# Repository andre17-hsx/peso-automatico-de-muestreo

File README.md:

# Automatic sampling scale reader

Automatically read the value shown by a **price-computing scale** (`ACS-JC36CV28` main board +
`WP-91110-2540-V7` display board, `CS2540` chip) and send it to a sampling system.

## Web panel

The ESP creates its own WiFi network and serves a mobile-first panel, with no internet or apps
needed: a replica of the scale's LED display, history grouped by BIN and mesh, CSV export,
light/dark mode and status alerts. The panel's user interface is in Spanish.

<table>
  <tr>
    <td align="center"><br><sub>Light mode</sub></td>
    <td align="center"><br><sub>Dark mode</sub></td>
    <td align="center"><br><sub>History by BIN and mesh</sub></td>
  </tr>
  <tr>
    <td align="center"><br><sub>Alert when a mesh is completed</sub></td>
    <td align="center"><br><sub>"SIN SEÑAL" (no signal) alert</sub></td>
    <td></td>
  </tr>
</table>

<sub>Screenshots with sample data: the real panel fed by a simulated ESP, not real measurements.</sub>

## Chosen approach: tap the display bus

Over **2 wires** (`DA` = data, `SL` = clock), the main board sends the display board the content
of the 3 displays (WEIGHT 5 digits, PRICE 5, TOTAL 6 = **16 digits**).
The `CS2540` chip is equivalent to a **TM1640**.

Listening to those 2 lines **passively** gives the exact value the scale shows, without touching
the measuring circuit and without the lighting/OCR problems of a camera.

No logic analyzer is needed: an **ESP32 / ESP32-S3** acts as the sniffer.

## Sketches

| Folder | Board | What it does |
|---|---|---|
| [`sniffer_tm1640/`](sniffer_tm1640/) | any ESP32/ESP32-S3 (Heltec V3) | sniffer only; dumps the display RAM over USB serial. Used to reverse-engineer the protocol. |
| [`peso_balanza_cam/`](peso_balanza_cam/) | **ESP32-S3 Super Mini** | **Final firmware**: bus sniffer + weighing history with meshes/BIN + web panel over WiFi. |

> Sniffer on **GPIO1 (SL) / GPIO4 (DA)**, with a **Schottky diode** in series on DA in addition
> to the 470 Ω resistor. Arduino IDE: "ESP32S3 Dev Module", 4 MB flash, PSRAM `Disabled`,
> **USB CDC On Boot `Enabled`** (the board has no CH340).
> See [`peso_balanza_cam/README.md`](peso_balanza_cam/README.md) (in Spanish).

## Phase 1 — Reverse-engineering the protocol (`sniffer_tm1640/` sketch)

### How it is tapped and decoded

The scale's numbers are **7-segment LEDs**. The main board does not send the display the number
"41.30", but **which segments to light in each digit**, over a 2-wire bus understood by the
`CS2540` chip (TM1640 family):

- `SL` = clock: each bit is valid on the **rising edge** of `SL`. `DA` = data: 8 bits per byte,
  **least significant bit first**.
- **START** = `DA` falls while `SL` is high · **STOP** = `DA` rises while `SL` is high (like I²C,
  but without ACK).
- The frame that matters starts with `0xC0 | address` and continues with **1 byte per digit** (16 in
  total: the display "RAM"). Mode (`0x40`) and brightness (`0x80…0x8F`) commands are ignored.

One display update at a glance (the ESP only listens, it never sends anything):

<p align="center">
  <picture>
    <source media="(prefers-color-scheme: dark)" srcset="docs/trama-oscuro.svg">
    
  </picture>
</p>

**Tapping = listening without touching.** `SL` and `DA` go into two ESP32 pins (with 470 Ω in
series, a Schottky diode on `DA` and a common GND) and the ESP **never writes to the bus**. Two
interrupts do all the work:

1. **Rising edge of `SL`** → read `DA` and build the byte bit by bit.
2. **`DA` change while `SL` is high** → START (a frame begins) or STOP (it ends, and its bytes are
   copied to a 16-byte mirror RAM).

The bus clock is about 140 kHz, so a normal ESP32-S3 interrupt keeps up without special hardware.
The copy is read once the bus has been quiet for a few milliseconds, so a half-finished refresh
is never read.

**Decoding = turning those 16 bytes into numbers:**

| Bytes | Field | Digits |
|---|---|---|
| 0–4 | WEIGHT | 5 |
| 5–9 | UNIT PRICE | 5 |
| 10–15 | TOTAL PRICE | 6 (on the board the last two are swapped: 15 comes before 14) |

- **Byte → digit:** bits 0–6 are segments `a`–`g` and bit 7 is the decimal point. A 7-segment
  table translates it (`0x3F` = "0", `0x06` = "1", `0x7F` = "8"…), including "blank" and the
  "−" sign (segment `g` only).
- **Digits → value:** the digits are joined right-aligned within the field and the decimal point
  is placed (WEIGHT and TOTAL: 2 fixed decimals; PRICE: wherever the scale lights the point, or an
  integer).
- **Robustness:** an icon (NET/TARE…) overlapping a digit is tolerated (1 segment of difference),
  and for what the panel shows, a refresh corrupted by noise is discarded because it differs from
  its neighbours. "Stable" is not on the bus: the ESP computes it when the weight has been the
  same for 4 refreshes in a row.

Which byte is which digit and which bit is which segment is exactly what the procedure below
finds out; on this scale it turned out to be the standard mapping (`a` = bit 0 … `g` = bit 6,
point = bit 7).

### Wiring (3 wires)

| Scale (DIS connector) | → | ESP32 |
|---|---|---|
| `DA`  | `[470 Ω]` | GPIO `PIN_DA` (default 4) |
| `SL`  | `[470 Ω]` | GPIO `PIN_SL` (default 5) |
| `GND` | — | `GND` (common ground, **required**) |

- Do **NOT** connect `VCC_DIS`.
- 3 V logic → goes straight into the ESP32-S3 GPIO, no level shifter needed.
- Recommended: a **Schottky diode** (BAT54 / 1N5817) in series on `DA`, anode toward the scale
  (see `peso_balanza_cam/README.md`, section 2).
- During the test: scale on **its own battery** (not the mains charger), ESP32 over USB.
- Set `PIN_DA` / `PIN_SL` in the `.ino` to two free GPIOs of your board (range 0–31).

### Procedure

1. Flash `sniffer_tm1640.ino`. Open the Serial Monitor at **115200**.
2. **Turn on the scale** → the segment self-test is captured (all segments on).
3. Enter **known** values and write down what each display shows at each moment:
   - empty and at zero
   - reference weight (e.g. 500 g) → `0.500`
   - another weight → `1.234`
   - price on the keypad: `1.00`, `9.99`, `12.50`
   - unstable vs stable platform (STABLE icon)
   - tare / zero
4. Copy the **whole** log and analyze it to deduce:
   - which byte (`D00`–`D15`) corresponds to which physical digit of which display
   - which bit of each byte is which segment (a–g) and which is the decimal point
   - which leftover bits are icons (`kg`/`lb`, STABLE, ZERO, TARE, NET, battery…)

Serial Monitor commands: `d` normal · `c` raw transactions · `f` statistics ·
`r` raw edge dump (only if decoding comes out as garbage).

## Phase 2 — Final firmware (done: `peso_balanza_cam/`)

With the map from Phase 1, the firmware:
- Listens passively → rebuilds the 16 bytes on every refresh.
- Applies the map → WEIGHT, PRICE, TOTAL, decimal points, and works out whether the weight is
  stable.
- Detects when a tray is removed and saves **one weighing** (it tells a tare from a real
  removal); all weighings are kept (they survive power cuts) until *Borrar todo* (clear all) is
  pressed: the last 120 in NVS and the full history in a file in flash (LittleFS).
- Captures the value with a **tolerant window** (it accepts the weight even if the product drips
  or the load cell bounces, and never saves a value from the drop to zero when the tray is
  removed).
- Keeps a **diagnostic log** in RAM (`/log`, downloadable from the phone): weighings saved/lost
  and why, WiFi connections and signal, reboots, program stalls.
- The panel shows a red **"SIN SEÑAL"** (no signal) bar when it stops receiving data from the
  ESP.
- Groups the weighings into **meshes and BINs** with targets typed in by the operator, and shows
  a pop-up when a group is closed.
- Publishes everything over WiFi on a **web panel** (the board creates its own network) and
  exports CSV.

Pending: sending to an external server (MQTT / HTTP). There is a ready hook, `weighOnCommit()`,
that fires once for every confirmed weighing.

### Assembly

The scale's metal housing blocks WiFi: the ESP32-S3 goes in an **external plastic box**, powered
from the scale's battery through a buck-boost converter (TPS63020) at 3.3 V. Two 5 V fans, each
switched by a 2N2222, cool the box according to the chip temperature. Full wiring diagram of the
box:

<p align="center">
  <picture>
    <source media="(prefers-color-scheme: dark)" srcset="docs/esquema-caja-oscuro.svg">
    
  </picture>
</p>

Details (materials, polarities, transistor calculation) are in the *Alimentación y montaje* and
*Ventilación de la caja* sections of `peso_balanza_cam/README.md` (in Spanish).

### Printed circuit board

The box circuit is also designed as a 2-layer through-hole PCB (KiCad 10, generated by script,
with ERC, DRC and schematic-to-PCB parity at zero). There are three versions in
[`hardware/pcb/`](hardware/pcb/):

| Version | Size | What changes |
|---|---|---|
| [v1](hardware/pcb/) | 70 × 50 mm | TPS63020 module off-board, connected through a 4-way terminal block |
| [v2](hardware/pcb/v2/) | 96 × 53 mm | All terminal blocks in one row on one edge; TPS63020 module mounted on the board |
| [v3](hardware/pcb/v3/) | 70 × 50 mm | v1 with the TPS63020 module mounted on the board |

## If the interrupt-based sniffer loses bits

Symptoms: the 16 bytes are inconsistent between refreshes, or the self-test does not give
`0xFF` in all of them.

Options, in order:
1. Use the `r` command and send the raw edge dump → it is decoded offline.
2. Version with hardware capture (the ESP32-S3 **I2S / LCD_CAM** peripheral, `SL` as clock,
   `DA` as data, via DMA) — immune to the bus speed.
3. Raspberry Pi Pico (~€4) as a logic analyzer with sigrok firmware (*pico logic analyzer*
   project), easier to get than a Saleae.

## Last resort: camera + OCR

Reading the display with a camera (classic 7-segment recognition) was tried before moving to the
sniffer, and was dropped: the sniffer gives the **exact** value straight from the bus, without
depending on light or framing, so it is the only method left in `peso_balanza_cam/`. If the camera
approach were ever needed again, it is in the git history (commits before the 2026-10-01
cleanup). If the bus cannot be tapped on a different scale, the idea would still be valid: an
ESP32-CAM fixed in front of the display, locked exposure, a ROI crop per digit, validation over
several frames (and, if the digits confuse 3/5/6/8/9, a trained CNN instead of segment decoding).

## License

Code published **for reference and as a work sample (portfolio) only**. All rights reserved: it
may not be copied, modified, redistributed, sold or used in other projects without written
permission. Details in [`LICENSE`](LICENSE).

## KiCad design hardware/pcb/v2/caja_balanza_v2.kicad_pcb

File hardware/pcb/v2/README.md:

# Box PCB (v2): terminal blocks in one row, TPS63020 on the board

Same circuit as v1 (parent folder) with three changes:

1. **All terminal blocks in one row** on the bottom edge, with the wire entry facing outward.
2. **The TPS63020 module is mounted on the board** (U2), like the ESP, instead of terminal block J3.
3. R2 and R4 (10k) lie flat, like the other resistors.

2-layer board, **96 × 53 mm** (v1 is 70 × 50 mm).

```
 ┌──────────────────────────────────────────────────────────────────────────────┐
 │  FAN1     FAN2   │  ESP32-S3 (USB-C up)      │ C2  ┌─ U2 TPS63020 ──────┐  C8 │
 │  R 470    R 470  │                           │ C3  │ OUTPUT     INPUT   │     │
 │  R 10k    R 10k  │                           │     └────────────────────┘     │
 │  Q1       Q2     │                           │                C1   F2         │
 │  C5       C6     │   sniffer: R5 R6 D3       │   F1                           │
 │  D1       D2     │                           │                   C4   C7      │
 │ [FAN1] [FAN2]    │      [DISPLAY]            │ [BAT] [SW]                     │
 └──────────────────────────────────────────────────────────────────────────────┘
```

| Terminal block | Terminals (left → right) | Goes to |
|---|---|---|
| J4 | FAN1+, FAN1- | Fan 1 |
| J5 | FAN2+, FAN2- | Fan 2 |
| J6 DISPLAY | SL, DA, GND | Display connector |
| J1 BATERIA | BAT+, BAT- | Scale battery |
| J2 INTERRUPTOR | SW, SW | Panel switch |

Each terminal has its name printed on both sides of the board: above the screw and below the pad.
The silkscreen is in Spanish (BATERIA = battery, INTERRUPTOR = switch, VENTILADORES = fans,
ENTRADA = input, SALIDA = output).

## TPS63020 module (U2)

- It is **rotated 180°** relative to how its own silkscreen reads: the **output (OUT, GND) is on
  the left**, toward the ESP, and the **input (VIN, GND) on the right**. The board shows the
  module outline and the SALIDA / ENTRADA, VIN and OUT labels; the square pad is VIN.
- It is mounted with **4 male pins** soldered into the module's corner holes. The pins are either
  soldered straight to the board, or plugged into 4 loose female sockets if it must be removable.
- **Output jumper on 3V3** (the module's 3V3 / 4V2 / 5V pads). Check it before plugging in the
  ESP: 4V2 or 5V will damage it.
- EN and PS are not connected: the module already handles them (it starts enabled). If it gives no
  output when tested, tie EN to VIN on the module itself.
- The recommendations of TI's TPS63020 datasheet (section 10.1) are followed. The ones internal to
  the regulator (inductor, capacitors right at the chip, control ground and FB divider) are
  already met by the module. On this board:
  - C8 (10 µF) sits right at the module's VIN, and C2 (470 µF) and C3 (100 nF) at its output and
    at the ESP's 3V3 pin.
  - The 3V3 track is about 15 mm long (in v1 it was about 70 mm through the terminal block and the
    wires).
  - Wide tracks: VBAT 1.0 mm, 3V3 0.8 mm.
  - Both module grounds go straight into the ground plane, which covers both layers.
  - The display signals run far from the module.

**Measure before ordering:** the centre-to-centre distance between the module's holes. The board
uses **24.0 mm** (horizontal) × **12.4 mm** (vertical), estimated from a photo. If they do not
match, change `TPS_DX` and `TPS_DY` in `gen_pcb_v2.py` and regenerate.

## Files

| File | Purpose |
|---|---|
| `fab/caja_balanza_v2_gerber_JLCPCB.zip` | Gerbers and drill files for JLCPCB / PCBWay |
| `esquema_caja_balanza_v2.pdf` | v2 schematic |
| `caja_balanza_v2.kicad_pro` | KiCad 10 project (linked board and schematic) |
| `BOM.csv` | Bill of materials |
| `render_*.png` | 3D views (the TPS module has no 3D model: only its outline is shown) |

## Verification

| Check | Result |
|---|---|
| Schematic ERC | 0 errors, 0 warnings |
| Board DRC | 0 errors, 0 warnings, 0 unconnected pads |
| Schematic ↔ board parity | 0 differences |
| `check_routing.py` | 0 problems (65 segments): no 90° corners, no acute angles, widths per class |

Routing rules, the other measurements to check, assembly and the first test are the same as in
the v1 README. In the first test (without the ESP), measure 3.3 V between the 3V3 and GND pins of
the ESP socket.

## Regenerate (from the parent folder)

```
set KP="C:\Program Files\KiCad\10.0\bin"
%KP%\python.exe gen_sch.py --v2
%KP%\python.exe gen_pcb_v2.py
cd v2
%KP%\kicad-cli.exe sch erc caja_balanza_v2.kicad_sch
%KP%\kicad-cli.exe pcb drc --refill-zones --save-board --schematic-parity caja_balanza_v2.kicad_pcb
%KP%\python.exe ..\check_routing.py caja_balanza_v2.kicad_pcb
```

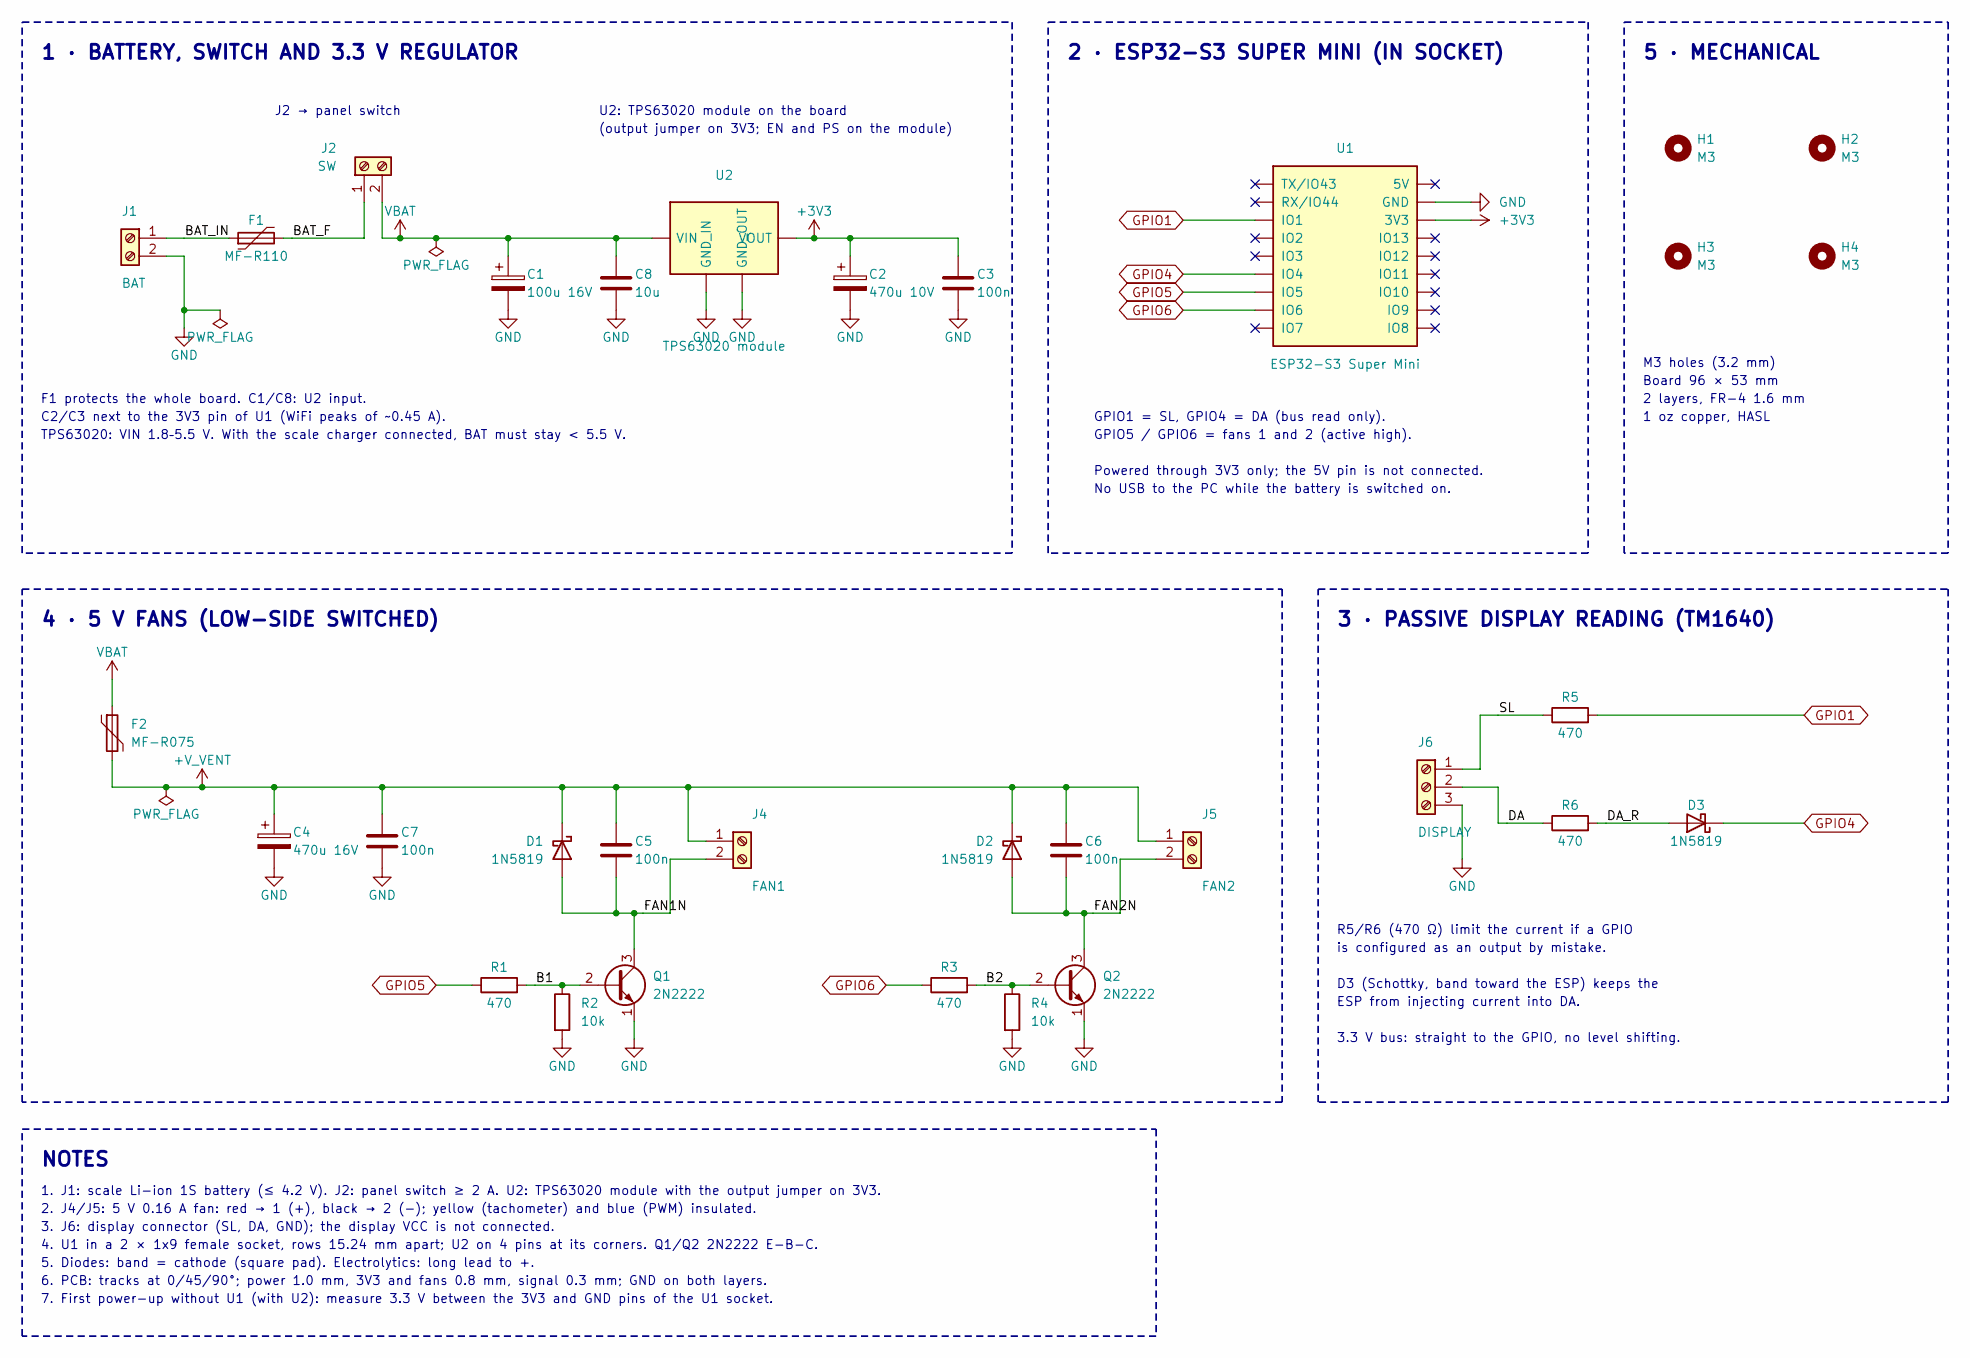
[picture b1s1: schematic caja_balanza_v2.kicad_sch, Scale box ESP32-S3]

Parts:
C1: 100u 16V; CP_Radial_D6.3mm_P2.50mm
C2: 470u 10V; CP_Radial_D8.0mm_P3.50mm
C3, C5, C6, C7: 100n; C_Disc_D5.0mm_W2.5mm_P5.00mm
C4: 470u 16V; CP_Radial_D8.0mm_P3.50mm
C8: 10u; C_Disc_D5.0mm_W2.5mm_P5.00mm
D1, D2: 1N5819; D_DO-41_SOD81_P10.16mm_Horizontal
D3: 1N5819; D_DO-41_SOD81_P7.62mm_Horizontal
F1: MF-R110; C_Disc_D7.5mm_W5.0mm_P5.00mm
F2: MF-R075; C_Disc_D7.5mm_W5.0mm_P5.00mm
H1, H2, H3, H4: M3; MountingHole_3.2mm_M3
J1: BAT; TerminalBlock_Phoenix_MKDS-1,5-2-5.08_1x02_P5.08mm_Horizont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
J2: SW; TerminalBlock_Phoenix_MKDS-1,5-2-5.08_1x02_P5.08mm_Horizont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
J4: FAN1; TerminalBlock_Phoenix_MKDS-1,5-2-5.08_1x02_P5.08mm_Horizont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
J5: FAN2; TerminalBlock_Phoenix_MKDS-1,5-2-5.08_1x02_P5.08mm_Horizont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
J6: DISPLAY; TerminalBlock_Phoenix_MKDS-1,5-3-5.08_1x03_P5.08mm_Horizont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
Q1, Q2: 2N2222; TO-92_Inline_Wide
R1, R3, R5, R6: 470; R_Axial_DIN0207_L6.3mm_D2.5mm_P7.62mm_Horizontal
R2, R4: 10k; R_Axial_DIN0207_L6.3mm_D2.5mm_P7.62mm_Horizontal
U1: ESP32-S3 Super Mini; ESP32-S3_SuperMini_Socket
U2: TPS63020 module; TPS63020_Module_26x18

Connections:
+3V3: C2.1, C3.1, U1.3V3, U2.4 (VOUT)
+V_VENT: C4.1, C5.1, C6.1, C7.1, D1.1 (K), D2.1 (K), F2.2, J4.1, J5.1
/B1: Q1.2 (B), R1.2, R2.1
/B2: Q2.2 (B), R3.2, R4.1
/BAT_F: F1.2, J2.1
/BAT_IN: F1.1, J1.1
/DA: J6.2, R6.1
/DA_R: D3.2 (A), R6.2
/FAN1N: C5.2, D1.2 (A), J4.2, Q1.3 (C)
/FAN2N: C6.2, D2.2 (A), J5.2, Q2.3 (C)
/SL: J6.1, R5.1
GND: C1.2, C2.2, C3.2, C4.2, C7.2, C8.2, J1.2, J6.3, Q1.1 (E), Q2.1 (E), R2.2, R4.2, U1.GND, U2.2 (GND_IN), U2.3 (GND_OUT)
GPIO1: R5.2, U1.1 (IO1)
GPIO4: D3.1 (K), U1.4 (IO4)
GPIO5: R1.1, U1.5 (IO5)
GPIO6: R3.1, U1.6 (IO6)
VBAT: C1.1, C8.1, F2.1, J2.2, U2.1 (VIN)

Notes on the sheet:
1 · BATTERY, SWITCH AND 3.3 V REGULATOR
J2 → panel switch
U2: TPS63020 module on the board
(output jumper on 3V3; EN and PS on the module)
F1 protects the whole board. C1/C8: U2 input.
C2/C3 next to the 3V3 pin of U1 (WiFi peaks of ~0.45 A).
TPS63020: VIN 1.8–5.5 V. With the scale charger connected, BAT must stay < 5.5 V.
2 · ESP32-S3 SUPER MINI (IN SOCKET)
GPIO1 = SL, GPIO4 = DA (bus read only).
GPIO5 / GPIO6 = fans 1 and 2 (active high).
Powered through 3V3 only; the 5V pin is not connected.
No USB to the PC while the battery is switched on.
5 · MECHANICAL
M3 holes (3.2 mm)
Board 96 × 53 mm
2 layers, FR-4 1.6 mm
1 oz copper, HASL
4 · 5 V FANS (LOW-SIDE SWITCHED)
3 · PASSIVE DISPLAY READING (TM1640)
R5/R6 (470 Ω) limit the current if a GPIO
is configured as an output by mistake.
D3 (Schottky, band toward the ESP) keeps the
ESP from injecting current into DA.
3.3 V bus: straight to the GPIO, no level shifting.
NOTES
1. J1: scale Li-ion 1S battery (≤ 4.2 V). J2: panel switch ≥ 2 A. U2: TPS63020 module with the output jumper on 3V3.
2. J4/J5: 5 V 0.16 A fan: red → 1 (+), black → 2 (−); yellow (tachometer) and blue (PWM) insulated.
3. J6: display connector (SL, DA, GND); the display VCC is not connected.
4. U1 in a 2 × 1x9 female socket, rows 15.24 mm apart; U2 on 4 pins at its corners. Q1/Q2 2N2222 E-B-C.
5. Diodes: band = cathode (square pad). Electrolytics: long lead to +.
6. PCB: tracks at 0/45/90°; power 1.0 mm, 3V3 and fans 0.8 mm, signal 0.3 mm; GND on both layers.
7. First power-up without U1 (with U2): measure 3.3 V between the 3V3 and GND pins of the U1 socket.

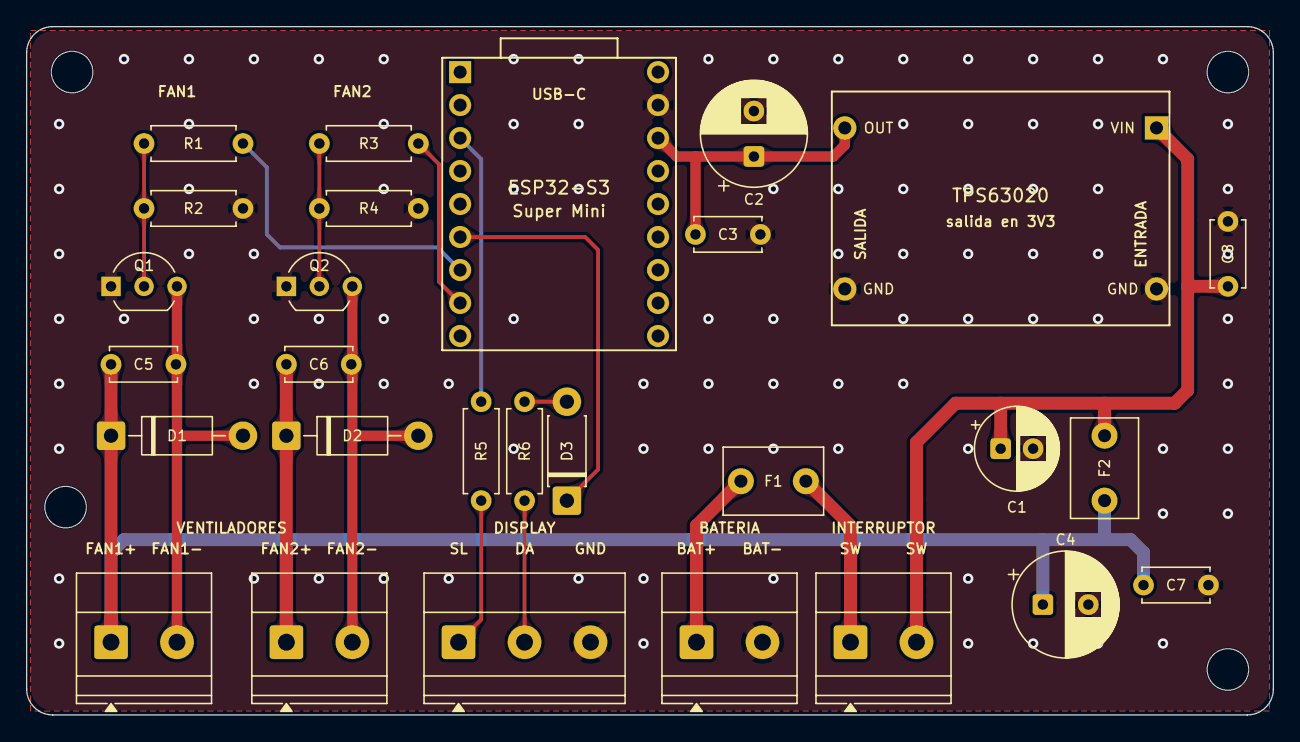
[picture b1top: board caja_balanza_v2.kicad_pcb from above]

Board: 2 copper layers, 96.0 x 53.0 mm, 32 parts (0 on the bottom side), 17 nets.

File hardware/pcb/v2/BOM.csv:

Ref;Qty;Value;Package / footprint;Note
U1;1;ESP32-S3 Super Mini;2 x 1x9 female headers, 2.54 mm (rows 15.24 mm apart);The ESP keeps its male headers soldered and plugs in
J1;1;2-way terminal block (BAT - / +);5.08 mm, KF301 / MKDS 1.5 type;Scale battery
J2;1;2-way terminal block (SWITCH);5.08 mm;To the SW1 panel switch (>= 2 A)
U2;1;TPS63020 buck-boost module (26 x 18 mm);4 male pins at the corners (or 4 loose female sockets on the board);Output jumper on 3V3, EN and PS not connected (handled by the module)
J4 J5;2;2-way terminal block (FAN + / -);5.08 mm;Red to +, black to -
J6;1;3-way terminal block (SL DA GND);5.08 mm;To the display connector
F1;1;PTC 1.1 A hold (MF-R110);radial, 5.1 mm lead pitch;Protects the whole board
F2;1;PTC 0.75 A hold (MF-R075);radial, 5.1 mm lead pitch;Fan branch only
C1;1;100 uF 16 V 105 C;electrolytic D6.3 mm, 2.5 mm pitch;Bulk VBAT, next to the switch
C8;1;10 uF 16 V X7R;ceramic, 5 mm pitch;Next to U2 VIN
C2;1;470 uF 10 V 105 C;electrolytic D8 mm, 3.5 mm pitch;WiFi peaks, next to the 3V3 pin
C3 C5 C6 C7;4;100 nF 50 V (104);ceramic, 5 mm pitch;Decoupling and motor noise
C4;1;470 uF 16 V 105 C;electrolytic D8 mm, 3.5 mm pitch;Fan start-up
R1 R3 R5 R6;4;470 ohm 1/4 W;axial, 7.62 mm pitch (lying flat);yellow-violet-brown
R2 R4;2;10 kohm 1/4 W;axial, 7.62 mm pitch (lying flat);brown-black-orange
Q1 Q2;2;2N2222 / PN2222A;TO-92, legs spread to 2.54 mm;E-B-C order (square = E), check with a multimeter
D1 D2;2;1N5819;DO-41, 10.16 mm pitch;Band toward the square pad (cathode, +V_VENT side)
D3;1;1N5819 (or BAT85);DO-41, 7.62 mm pitch;Band toward the ESP (square pad)
H1-H4;4;M3 screw + standoff;3.2 mm hole;

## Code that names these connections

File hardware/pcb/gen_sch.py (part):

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j1 = part("J1", "Connector:Screw_Terminal_01x02", 27.94, RAIL, mirror=True,
          fields={"Reference": fld(-1.27, -3.81, "right"), "Value": fld(-1.27, 6.35, "right")})
f1 = part("F1", "Device:Polyfuse", 45.72, RAIL, rot=90, fields=H2)
W(j1.pin(1), f1.pin(1)); label("BAT_IN", 35.56, RAIL)
W(j1.pin(2), (35.56, j1.pin(2)[1]), (35.56, 58.42)); power("power:GND", 35.56, 58.42)
W((35.56, 55.88), (40.64, 55.88)); power("power:PWR_FLAG", 40.64, 55.88, rot=180)
j2 = part("J2", "Connector:Screw_Terminal_01x02", 60.96, 35.56, rot=90,
          fields={"Reference": fld(-3.81, -2.54, "right"), "Value": fld(-3.81, 0, "right")})
W(f1.pin(2), (j2.pin(1)[0], RAIL), j2.pin(1)); label("BAT_F", 50.8, RAIL)
if TPS_EN_PLACA:
    u2 = Sym("U2", TPS_LIB_ID, 111.76, RAIL,
             fields={"Reference": fld(0, -8.89), "Value": fld(0, 15.24)})
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OFF[:] = [-3.81, -2.54]
u1 = Sym("U1", ESP_LIB_ID, 203.2, 48.26,
         fields={"Reference": fld(0, -15.24), "Value": fld(0, 15.24)})
for num, net_ in (("1", "GPIO1"), ("4", "GPIO4"), ("5", "GPIO5"), ("6", "GPIO6")):
    p = u1.pin(num)
    W(p, (180.34, p[1])); glabel(net_, 180.34, p[1], 180)
pg, p3 = u1.pin("GND"), u1.pin("3V3")
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for num, _ in LEFT + RIGHT:
    if num not in ("1", "4", "5", "6", "GND", "3V3"):
        nc(u1.pin(num))
text("GPIO1 = SL, GPIO4 = DA (bus read only).", 167.64, 71.12)
text("GPIO5 / GPIO6 = fans 1 and 2 (active high).", 167.64, 73.66)
text("Powered through 3V3 only; the 5V pin is not connected.", 167.64, 78.74)
text("No USB to the PC while the battery is switched on.", 167.64, 81.28)

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r6 = part("R6", "Device:R", 292.1, 66.04, rot=90, fields=H2)
d3 = part("D3", "Diode:1N5819", 309.88, 66.04, rot=180, fields=H2)
W(j6.pin(1), (279.4, j6.pin(1)[1]), (279.4, 50.8), r5.pin(1)); label("SL", 281.94, 50.8)
W(r5.pin(2), (325.12, 50.8)); glabel("GPIO1", 325.12, 50.8, 0)
W(j6.pin(2), (281.94, j6.pin(2)[1]), (281.94, 66.04), r6.pin(1)); label("DA", 283.21, 66.04)
W(r6.pin(2), d3.pin(2)); label("DA_R", 297.18, 66.04)
W(d3.pin(1), (325.12, 66.04)); glabel("GPIO4", 325.12, 66.04, 0)
W(j6.pin(3), (j6.pin(3)[0], 71.12)); power("power:GND", j6.pin(3)[0], 71.12)
text("R5/R6 (470 Ω) limit the current if a GPIO", 259.08, 81.28)
text("is configured as an output by mistake.", 259.08, 83.82)
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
